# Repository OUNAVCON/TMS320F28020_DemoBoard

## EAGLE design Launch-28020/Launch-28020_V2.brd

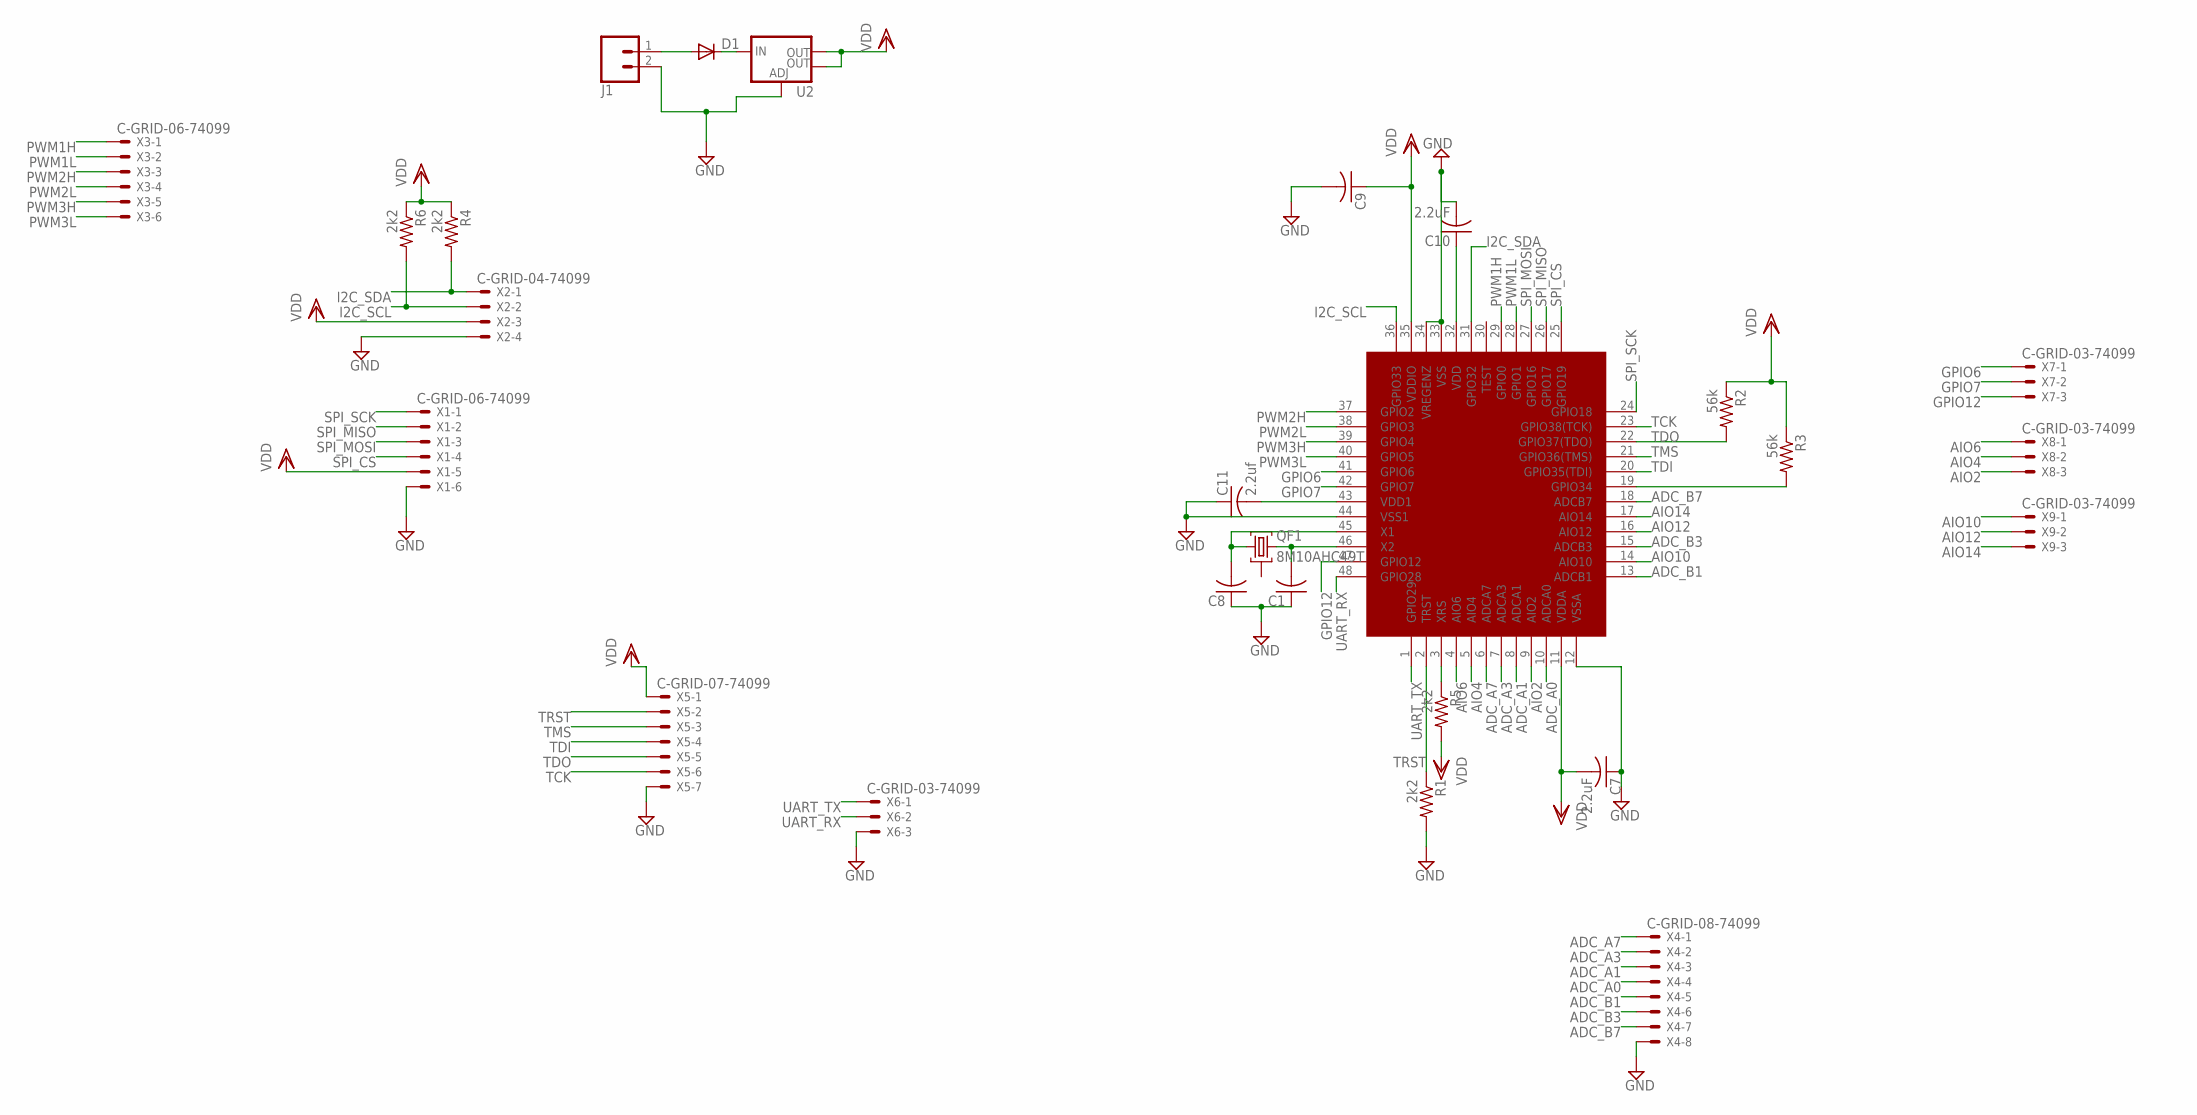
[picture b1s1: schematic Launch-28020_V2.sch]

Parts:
C1, C8, C9: C-USC1206; C1206
C7, C10: 2.2uF; C1206
C11: 2.2uf; C1206
D1: DIODE-SOD106-W; SOD106-W
J1: CONN_023.5MM-NO_SILK; SCREWTERMINAL-3.5MM-2-NS
QF1: 8M10AHC49T; HC49U
R1, R4, R5, R6: 2k2; M1206
R2, R3: 56k; M1206
U2: V_REG_LM1117SOT223; SOT223
U$1: TMS320F28020; LQFP-48
X1, X3: C-GRID-06-74099; 74099-06
X2: C-GRID-04-74099; 74099-04
X4: C-GRID-08-74099; 74099-08
X5: C-GRID-07-74099; 74099-07
X6, X7, X8, X9: C-GRID-03-74099; 74099-03

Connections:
ADC_A0: U$1.10 (ADCA0), X4.4
ADC_A1: U$1.8 (ADCA1), X4.3
ADC_A3: U$1.7 (ADCA3), X4.2
ADC_A7: U$1.6 (ADCA7), X4.1
ADC_B1: U$1.13 (ADCB1), X4.5
ADC_B3: U$1.15 (ADCB3), X4.6
ADC_B7: U$1.18 (ADCB7), X4.7
AIO2: U$1.9 (AIO2), X8.3
AIO4: U$1.5 (AIO4), X8.2
AIO6: U$1.4 (AIO6), X8.1
AIO10: U$1.14 (AIO10), X9.1
AIO12: U$1.16 (AIO12), X9.2
AIO14: U$1.17 (AIO14), X9.3
GND: C1.1, C7.1, C8.1, C9.2, C10.2, C11.1, J1.2, R1.2, U2.1 (ADJ), U$1.12 (VSSA), U$1.33 (VSS), U$1.34 (VREGENZ), U$1.44 (VSS1), X1.6, X2.4, X4.8, X5.7, X6.3
GPIO6: U$1.41 (GPIO6), X7.1
GPIO7: U$1.42 (GPIO7), X7.2
GPIO12: U$1.47 (GPIO12), X7.3
I2C_SCL: R6.2, U$1.36 (GPIO33), X2.2
I2C_SDA: R4.2, U$1.31 (GPIO32), X2.1
unnamed: D1.A, J1.1
unnamed: C10.1, U$1.32 (VDD)
unnamed: C11.2, U$1.43 (VDD1)
unnamed: R5.1, U$1.3 (XRS)
unnamed: C8.2, QF1.1, U$1.45 (X1)
unnamed: C1.2, QF1.3, U$1.46 (X2)
unnamed: D1.C, U2.3 (IN)
unnamed: R3.2, U$1.19 (GPIO34)
PWM1H: U$1.29 (GPIO0), X3.1
PWM1L: U$1.28 (GPIO1), X3.2
PWM2H: U$1.37 (GPIO2), X3.3
PWM2L: U$1.38 (GPIO3), X3.4
PWM3H: U$1.39 (GPIO4), X3.5
PWM3L: U$1.40 (GPIO5), X3.6
SPI_CS: U$1.25 (GPIO19), X1.4
SPI_MISO: U$1.26 (GPIO17), X1.2
SPI_MOSI: U$1.27 (GPIO16), X1.3
SPI_SCK: U$1.24 (GPIO18), X1.1
TCK: U$1.23 (GPIO38(TCK)), X5.6
TDI: U$1.20 (GPIO35(TDI)), X5.4
TDO: R2.2, U$1.22 (GPIO37(TDO)), X5.5
TMS: U$1.21 (GPIO36(TMS)), X5.3
TRST: R1.1, U$1.2 (TRST), X5.2
UART_RX: U$1.48 (GPIO28), X6.2
UART_TX: U$1.1 (GPIO29), X6.1
VDD: C7.2, C9.1, R2.1, R3.1, R4.1, R5.2, R6.1, U2.2 (OUT), U2.4 (OUT), U$1.11 (VDDA), U$1.35 (VDDIO), X1.5, X2.3, X5.1

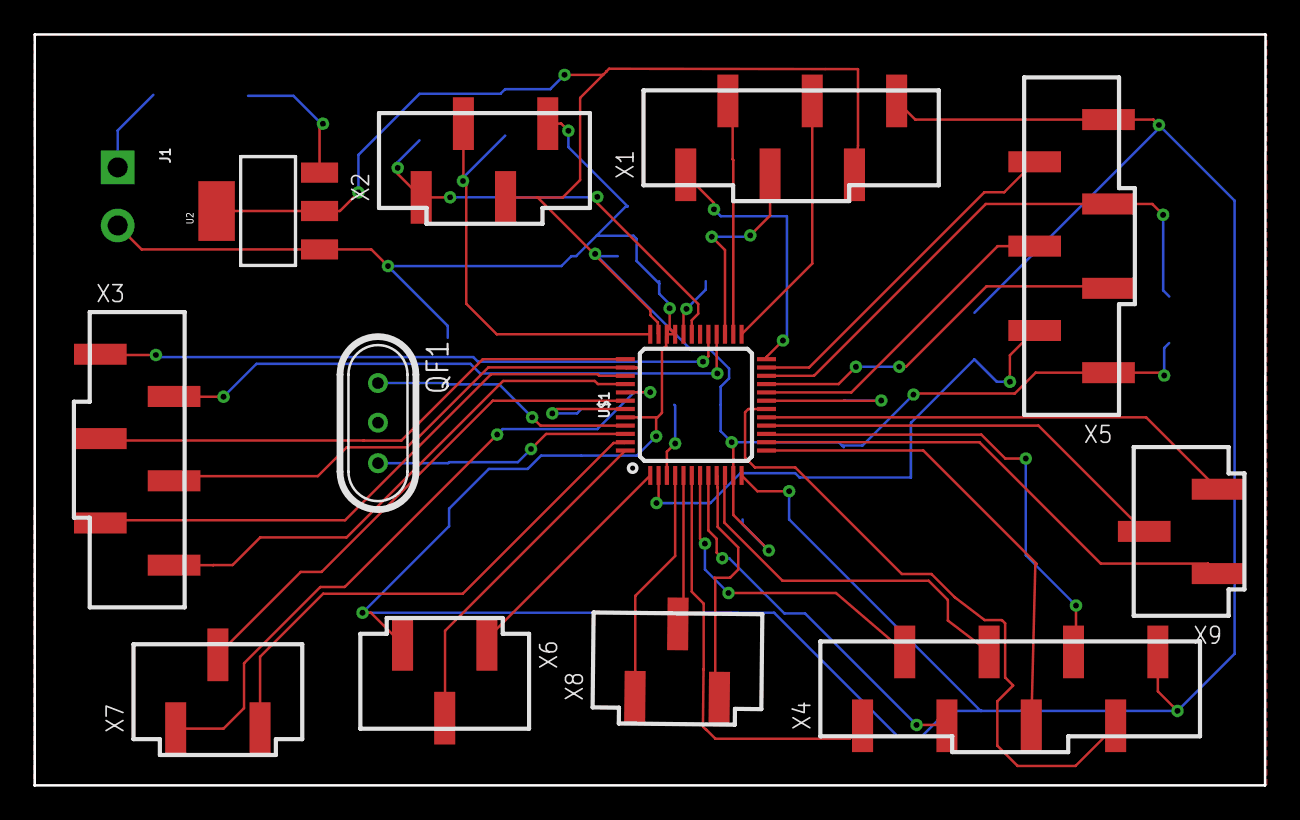
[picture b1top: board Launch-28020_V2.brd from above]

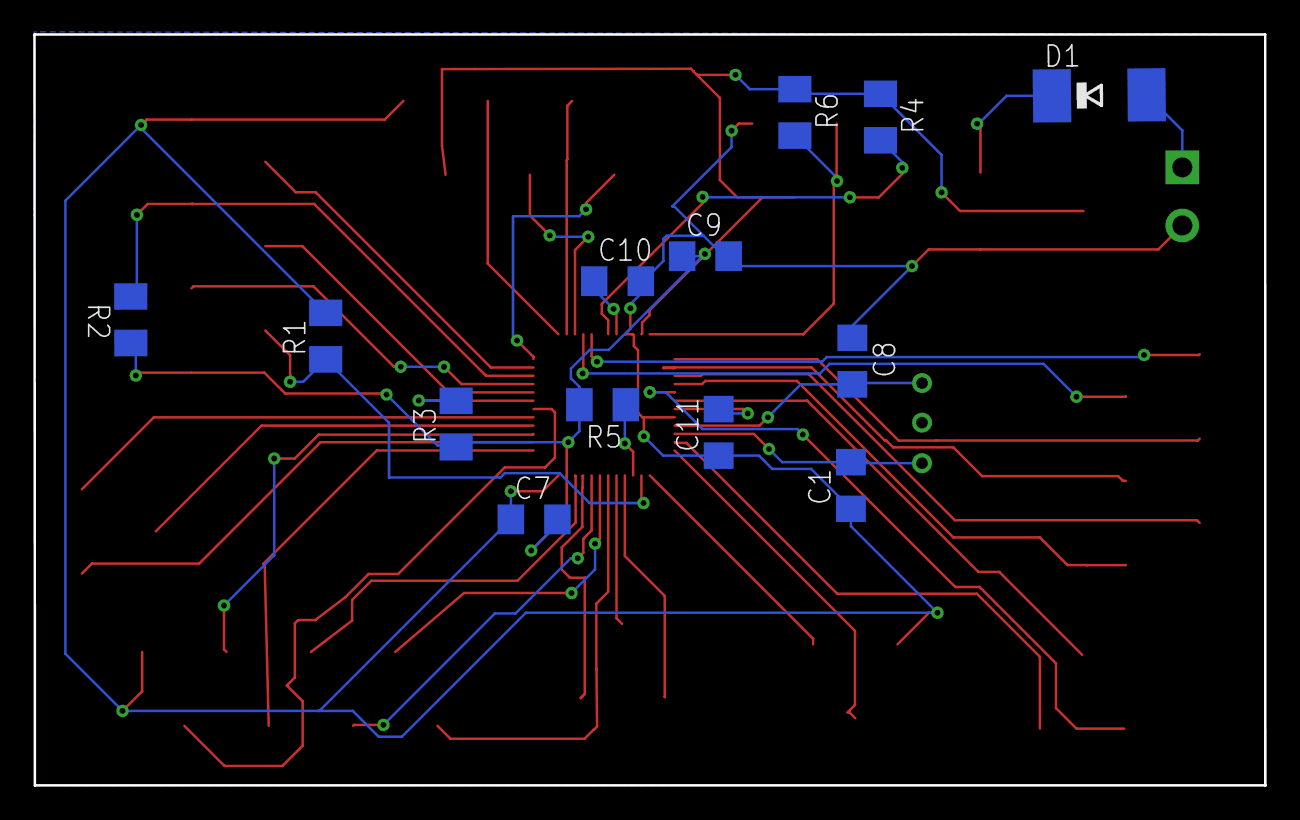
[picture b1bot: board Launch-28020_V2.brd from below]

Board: 2 copper layers, 74.1 x 45.2 mm, 26 parts (13 on the bottom side), 45 nets.

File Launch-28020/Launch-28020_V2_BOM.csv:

"Part";"Value";"Device";"Package";"Description";"MF";"MPN";"OC_FARNELL";"OC_NEWARK";"PROD_ID";
"C1";"";"C-USC1206";"C1206";"CAPACITOR, American symbol";"";"";"";"";"";
"C7";"2.2uF";"C-USC1206";"C1206";"CAPACITOR, American symbol";"";"";"";"";"";
"C8";"";"C-USC1206";"C1206";"CAPACITOR, American symbol";"";"";"";"";"";
"C9";"";"C-USC1206";"C1206";"CAPACITOR, American symbol";"";"";"";"";"";
"C10";"2.2uF";"C-USC1206";"C1206";"CAPACITOR, American symbol";"";"";"";"";"";
"C11";"2.2uf";"C-USC1206";"C1206";"CAPACITOR, American symbol";"";"";"";"";"";
"D1";"";"DIODE-SOD106-W";"SOD106-W";"DIODE";"";"";"";"";"";
"J1";"";"CONN_023.5MM-NO_SILK";"SCREWTERMINAL-3.5MM-2-NS";"Multi connection point. Often used as Generic Header-pin footprint for 0.1 inch spaced/style header connections";"";"";"";"";"CONN-08399";
"QF1";"8M10AHC49T";"8M10AHC49T";"HC49U";"Monolithic Crystal Filters";"";"";"unknown";"unknown";"";
"R1";"2k2";"R-US_M1206";"M1206";"RESISTOR, American symbol";"";"";"";"";"";
"R2";"56k";"R-US_M1206";"M1206";"RESISTOR, American symbol";"";"";"";"";"";
"R3";"56k";"R-US_M1206";"M1206";"RESISTOR, American symbol";"";"";"";"";"";
"R4";"2k2";"R-US_M1206";"M1206";"RESISTOR, American symbol";"";"";"";"";"";
"R5";"2k2";"R-US_M1206";"M1206";"RESISTOR, American symbol";"";"";"";"";"";
"R6";"2k2";"R-US_M1206";"M1206";"RESISTOR, American symbol";"";"";"";"";"";
"U$1";"TMS320F28020";"TMS320F28020";"LQFP-48";"";"";"";"";"";"";
"U2";"";"V_REG_LM1117SOT223";"SOT223";"Voltage Regulator LM1117";"";"";"";"";"VREG-08170";
"X1";"C-GRID-06-74099";"C-GRID-06-74099";"74099-06";"CONNECTOR";"";"";"unknown";"unknown";"";
"X2";"C-GRID-04-74099";"C-GRID-04-74099";"74099-04";"CONNECTOR";"";"";"unknown";"unknown";"";
"X3";"C-GRID-06-74099";"C-GRID-06-74099";"74099-06";"CONNECTOR";"";"";"unknown";"unknown";"";
"X4";"C-GRID-08-74099";"C-GRID-08-74099";"74099-08";"CONNECTOR";"";"";"unknown";"unknown";"";
"X5";"C-GRID-07-74099";"C-GRID-07-74099";"74099-07";"CONNECTOR";"";"";"unknown";"unknown";"";
"X6";"C-GRID-03-74099";"C-GRID-03-74099";"74099-03";"CONNECTOR";"";"";"unknown";"unknown";"";
"X7";"C-GRID-03-74099";"C-GRID-03-74099";"74099-03";"CONNECTOR";"";"";"unknown";"unknown";"";
"X8";"C-GRID-03-74099";"C-GRID-03-74099";"74099-03";"CONNECTOR";"";"";"unknown";"unknown";"";
"X9";"C-GRID-03-74099";"C-GRID-03-74099";"74099-03";"CONNECTOR";"";"";"unknown";"unknown";"";

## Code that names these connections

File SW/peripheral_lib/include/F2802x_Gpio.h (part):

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//
struct GPA1_BITS
{                                // bits   description
    uint16_t GPIO0:2;            // 1:0    GPIO0
    uint16_t GPIO1:2;            // 3:2    GPIO1
    uint16_t GPIO2:2;            // 5:4    GPIO2
    uint16_t GPIO3:2;            // 7:6    GPIO3
    uint16_t GPIO4:2;            // 9:8    GPIO4
    uint16_t GPIO5:2;            // 11:10  GPIO5
    uint16_t GPIO6:2;            // 13:12  GPIO6
    uint16_t GPIO7:2;            // 15:14  GPIO7
    uint16_t GPIO8:2;            // 17:16  GPIO8
    uint16_t GPIO9:2;            // 19:18  GPIO9
    uint16_t GPIO10:2;           // 21:20  GPIO10
    uint16_t GPIO11:2;           // 23:22  GPIO11
    uint16_t GPIO12:2;           // 25:24  GPIO12
    uint16_t GPIO13:2;           // 27:26  GPIO13
    uint16_t GPIO14:2;           // 29:28  GPIO14
    uint16_t GPIO15:2;           // 31:30  GPIO15
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
struct GPA2_BITS
{                                // bits   description
    uint16_t GPIO16:2;           // 1:0    GPIO16
    uint16_t GPIO17:2;           // 3:2    GPIO17
    uint16_t GPIO18:2;           // 5:4    GPIO18
    uint16_t GPIO19:2;           // 7:6    GPIO19
    uint16_t GPIO20:2;           // 9:8    GPIO20
    uint16_t GPIO21:2;           // 11:10  GPIO21
    uint16_t GPIO22:2;           // 13:12  GPIO22
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    uint16_t GPIO25:2;           // 19:18  GPIO25
    uint16_t GPIO26:2;           // 21:20  GPIO26
    uint16_t GPIO27:2;           // 23:22  GPIO27
    uint16_t GPIO28:2;           // 25:24  GPIO28
    uint16_t GPIO29:2;           // 27:26  GPIO29
    uint16_t GPIO30:2;           // 29:28  GPIO30
    uint16_t GPIO31:2;           // 31:30  GPIO31
};

struct GPB1_BITS
{                               // bits   description
    uint16_t GPIO32:2;           // 1:0    GPIO32
    uint16_t GPIO33:2;           // 3:2    GPIO33
    uint16_t GPIO34:2;           // 5:4    GPIO34
    uint16_t GPIO35:2;           // 7:6    GPIO35
    uint16_t GPIO36:2;           // 9:8    GPIO36
    uint16_t GPIO37:2;           // 11:10  GPIO37
    uint16_t GPIO38:2;           // 13:12  GPIO38
    uint16_t rsvd1:2;            // 15:14  reserved
    uint16_t rsvd2:16;           // 31:16  reserved
};

struct AIO_BITS
{                               // bits   description
    uint16_t rsvd1:2;           // 1:0    GPIO0
    uint16_t rsvd2:2;           // 3:2    GPIO1
    uint16_t AIO2:2;            // 5:4    GPIO2
    uint16_t rsvd3:2;           // 7:6    GPIO3
    uint16_t AIO4:2;            // 9:8    GPIO4
    uint16_t rsvd4:2;           // 11:10  GPIO5
    uint16_t AIO6:2;            // 13:12  GPIO6
    uint16_t rsvd5:2;           // 15:14  GPIO7
    uint16_t rsvd6:2;           // 17:16  GPIO8
    uint16_t rsvd7:2;           // 19:18  GPIO9
    uint16_t AIO10:2;           // 21:20  GPIO10
    uint16_t rsvd8:2;           // 23:22  GPIO11
    uint16_t AIO12:2;           // 25:24  GPIO12
    uint16_t rsvd9:2;           // 27:26  GPIO13
    uint16_t AIO14:2;           // 29:28  GPIO14
    uint16_t rsvd10:2;          // 31:30  GPIO15
};

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//
struct GPADAT_BITS
{                                // bits   description
    uint16_t GPIO0:1;            // 0      GPIO0
    uint16_t GPIO1:1;            // 1      GPIO1
    uint16_t GPIO2:1;            // 2      GPIO2
    uint16_t GPIO3:1;            // 3      GPIO3
    uint16_t GPIO4:1;            // 4      GPIO4
    uint16_t GPIO5:1;            // 5      GPIO5
    uint16_t GPIO6:1;            // 6      GPIO6
    uint16_t GPIO7:1;            // 7      GPIO7
    uint16_t GPIO8:1;            // 8      GPIO8
    uint16_t GPIO9:1;            // 9      GPIO9
    uint16_t GPIO10:1;           // 10     GPIO10
    uint16_t GPIO11:1;           // 11     GPIO11
    uint16_t GPIO12:1;           // 12     GPIO12
    uint16_t GPIO13:1;           // 13     GPIO13
    uint16_t GPIO14:1;           // 14     GPIO14
    uint16_t GPIO15:1;           // 15     GPIO15
    uint16_t GPIO16:1;           // 16     GPIO16
    uint16_t GPIO17:1;           // 17     GPIO17
    uint16_t GPIO18:1;           // 18     GPIO18
    uint16_t GPIO19:1;           // 19     GPIO19
    uint16_t GPIO20:1;           // 20     GPIO20
    uint16_t GPIO21:1;           // 21     GPIO21
    uint16_t GPIO22:1;           // 22     GPIO22
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    uint16_t GPIO25:1;           // 25     GPIO25
    uint16_t GPIO26:1;           // 26     GPIO26
    uint16_t GPIO27:1;           // 27     GPIO27
    uint16_t GPIO28:1;           // 28     GPIO28
    uint16_t GPIO29:1;           // 29     GPIO29
    uint16_t GPIO30:1;           // 30     GPIO30
    uint16_t GPIO31:1;           // 31     GPIO31
};

struct GPBDAT_BITS
{                                // bits   description
    uint16_t GPIO32:1;           // 0      GPIO32
    uint16_t GPIO33:1;           // 1      GPIO33
    uint16_t GPIO34:1;           // 2      GPIO34
    uint16_t GPIO35:1;           // 3      GPIO35
    uint16_t GPIO36:1;           // 4      GPIO36
    uint16_t GPIO37:1;           // 5      GPIO37
    uint16_t GPIO38:1;           // 6      GPIO38
    uint16_t rsvd1:9;            // 15:7   reserved
    uint16_t rsvd2:16;           // 31:16  reserved
};
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
struct GPIO_CTRL_REGS
{
    union  GPACTRL_REG  GPACTRL;   // GPIO A Control Register (GPIO0 to 31)
    
    //
    // GPIO A Qualifier Select 1 Register (GPIO0 to 15)
    //
    union  GPA1_REG     GPAQSEL1;
    
    //
    // GPIO A Qualifier Select 2 Register (GPIO16 to 31)
    //
    union  GPA2_REG     GPAQSEL2;
    
    union  GPA1_REG     GPAMUX1;   // GPIO A Mux 1 Register (GPIO0 to 15)
    union  GPA2_REG     GPAMUX2;   // GPIO A Mux 2 Register (GPIO16 to 31)
    union  GPADAT_REG   GPADIR;    // GPIO A Direction Register (GPIO0 to 31)
    
    //
    // GPIO A Pull Up Disable Register (GPIO0 to 31)
    //
    union  GPADAT_REG   GPAPUD;    
    
    uint32_t            rsvd1;     // reserved
    union  GPBCTRL_REG  GPBCTRL;   // GPIO B Control Register (GPIO32 to 38)
    
    //
    // GPIO B Qualifier Select 1 Register (GPIO32 to 38)
    //
    union  GPB1_REG     GPBQSEL1;
    
    uint32_t            rsvd2;     // reserved
    union  GPB1_REG     GPBMUX1;   // GPIO B Mux 1 Register (GPIO32 to 38)
    uint32_t            rsvd3;     // reserved
    
    //
    // GPIO B Direction Register (GPIO32 to 38)
    //
    union  GPBDAT_REG   GPBDIR;
    
    //
    // GPIO B Pull Up Disable Register (GPIO32 to 38)
    //
    union  GPBDAT_REG   GPBPUD;
    uint16_t            rsvd4[24]; // reserved
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
struct GPIO_DATA_REGS 
{
    union  GPADAT_REG       GPADAT;    // GPIO Data Register (GPIO0 to 31)
    
    //
    // GPIO Data Set Register (GPIO0 to 31)
    //
    union  GPADAT_REG       GPASET;
    
    //
    // GPIO Data Clear Register (GPIO0 to 31)
    //
    union  GPADAT_REG       GPACLEAR;
    
    //
    // GPIO Data Toggle Register (GPIO0 to 31)
    //
    union  GPADAT_REG       GPATOGGLE;
    
    union  GPBDAT_REG       GPBDAT;   // GPIO Data Register (GPIO32 to 38)
    
    //
    // GPIO Data Set Register (GPIO32 to 38)
    //
    union  GPBDAT_REG       GPBSET;
    
    
    //
    // GPIO Data Clear Register (GPIO32 to 38)
    //
    union  GPBDAT_REG       GPBCLEAR;
    
    //
    // GPIO Data Toggle Register (GPIO32 to 38)
    //
    union  GPBDAT_REG       GPBTOGGLE; 
    
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
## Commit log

2017-10-24 Added Software Project
2017-10-24 Added driver lib and IQ math library.
2017-10-24 Added peripheral lib
2017-10-25 fixed space issue when compiling. Only add in libs as needed
2017-10-30 Updated Schematic
2017-10-30 Added IO headeres
2017-11-03 Updated the schematic to include power circuitry and connectivity.
2017-11-13 Created a working schematic and board layout. THe laytout can be optimized there seens to be some extra board space for the ground plane. Could also use mounting holes.
2017-11-30 Inital Board Layout
2017-12-04 Updated build files.
2018-02-14 Updated Layout
2018-02-14 Added PDF of schematics and laytouts
2018-02-14 Added BOM
2018-03-02 Updated main based on sci example.
2018-03-05 PWM4 active, to be used as tick for control loop.
2018-03-06 Fixed issue where code would not start from flash without debugger
2018-03-12 Fixed device header file and added serial data transmitt.
2018-03-12 Added ADC sampling. Added interrupt for Sci TX. Still need to load sci buffer using tx until message is empty
2018-03-27 Added SPI and CAN code, but not functional

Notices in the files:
SW/peripheral_lib/include/F2802x_Gpio.h:
$Copyright:
Copyright (C) 2009-2017 Texas Instruments Incorporated - http://www.ti.com
parts and their libraries:
SparkFun-Connectors: Licensing: Creative Commons ShareAlike 4.0 International - https://creativecommons.org/licenses/by-sa/4.0
